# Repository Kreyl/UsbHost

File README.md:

# UsbHost
PCB with MCU &amp; CC1101, with USB connector

This project is for manupulating Ostranna devices from PC using radio
This branch is for Magic Stick project. There are two devices in system, host and wand https://github.com/Kreyl/MagicStick.
Wand sends raw data from IMU to host and host may send commands to wand.

Protocol descrideb here (in Russian) https://docs.google.com/document/d/1Enq7OxXN71MnZqI4T44DpILLiYlTNmURxSFmcvyZTgg/edit
List of commands in Russian https://docs.google.com/document/d/1xTNT9nXQbrqk0kijIyspimRIQRoJOtMbkZyYuiGS3eA/edit#heading=h.siqy2t4hsq6f
USB2Radio devices displays itself as virtual COM-port, you may user Terminal app to send commands or send commands from your code to serial port object. 

Archived branches are available here https://github.com/Kreyl/UsbHost/tags

We also have python module to work with USB2Radio  (in python folder). 

<details>
  <summary>Commands list:</summary> 

*get_port_list() function returns list of available comports as ['COM3', 'COM5', 'COM20' ...];

*get_device_port function returns first found port with Ostranna device (answer 'Ack 0' to 'Ping\r\n') as 'COM4';

*get_all_device_ports() returns list of comports with Ostranna devices connected 
                        (answer 'Ack 0' to 'Ping\r\n') as ['COM4', ...];

*open_port(port_id: str) takes comport as str parameter (open_port('COM4') and returns open port or None;

*send command(ser, command, parameters) send command with parameters to ser port, returns send status
              ("ok", "Bad data", "Unknown command" or "No device port") ;

*send query(ser, command, parameters) send query with parameters to ser port and returns answer;

*close_port(ser) gets result of open_port(port_id) as parameter and closes it .
</details>

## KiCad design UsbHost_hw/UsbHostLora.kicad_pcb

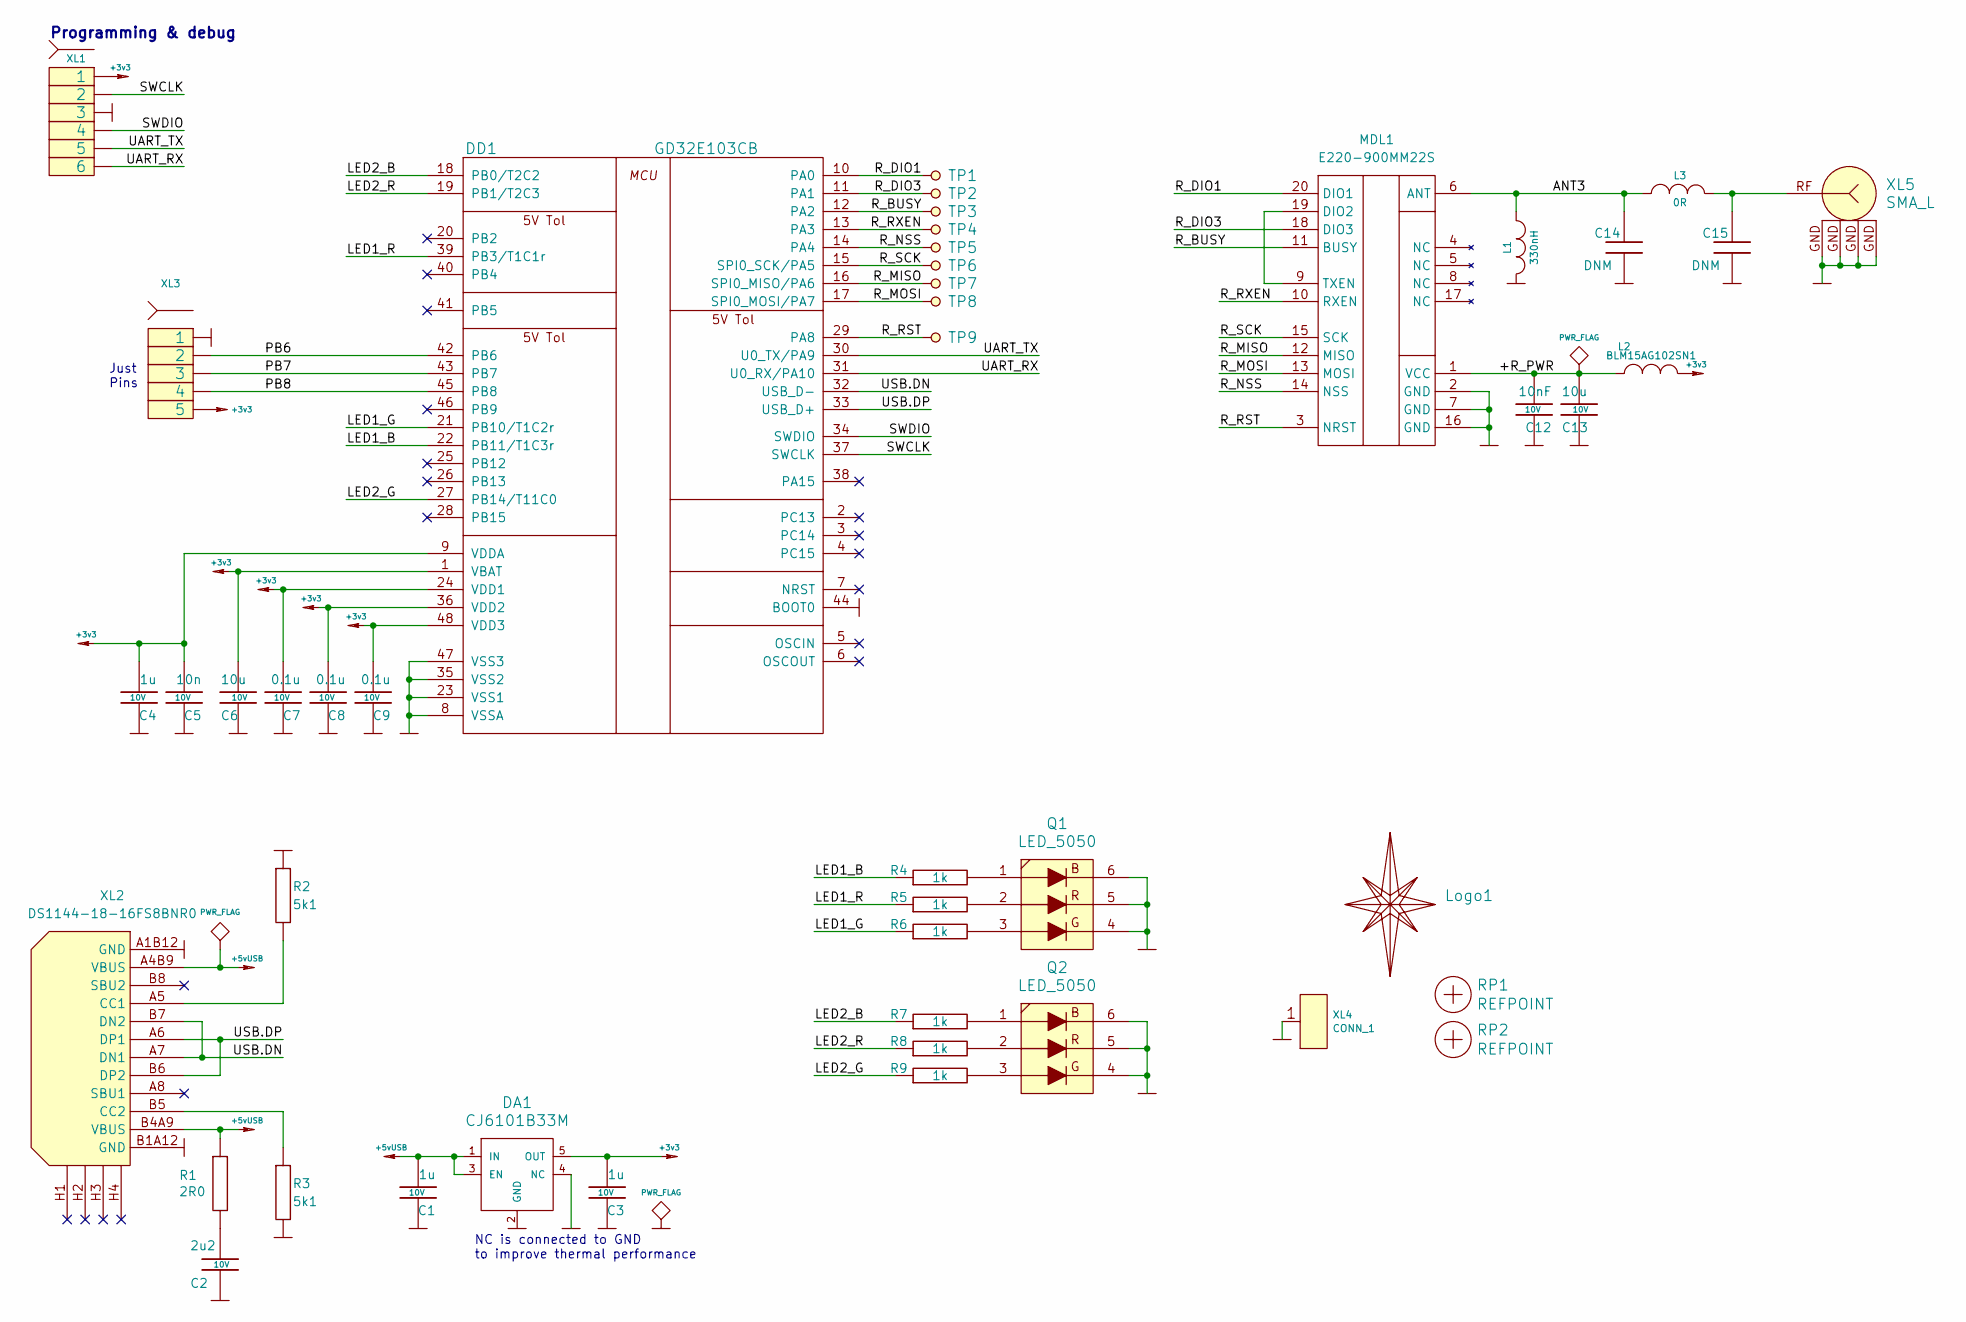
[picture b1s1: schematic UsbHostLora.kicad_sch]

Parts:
C1, C3, C4: 1u; CAP_0603_Silks; Tolerance 20%; Voltage 10V
C2: 2u2; CAP_0603_Silks; Tolerance 20%; Voltage 10V
C5: 10n; CAP_0603_Silks; Tolerance 20%; Voltage 10V
C6, C13: 10u; CAP_0603_Silks; Tolerance 20%; Voltage 10V
C7, C8, C9: 0.1u; CAP_0603_Silks; Tolerance 20%; Voltage 10V
C12: 10nF; CAP_0603_Silks; Tolerance 20%; Voltage 10V
C14, C15: DNM; CAP_0402_Silks; Tolerance 20%; Voltage 10V
DA1: CJ6101B33M; SOT23-5
DD1: GD32E103CB; LQFP48
L1: 330nH; IND_0402; Tolerance 20%
L2: BLM15AG102SN1; IND_0402; Tolerance 20%
L3: 0R; IND_0402; Tolerance 20%
Logo1: Logo; Ostranna_12d7_10d1
MDL1: E220-900MM22S
Q1, Q2: LED_5050
R1: 2R0; RES_0603_RefFab; Tolerance 1%
R2, R3: 5k1; RES_0603_RefFab; Tolerance 1%
R4, R5, R6, R7, R8, R9: 1k; RES_0603_RefFab; Tolerance 1%
RP1, RP2: REFPOINT; REF_POINT_1MM
TP1, TP2, TP3, TP4, TP5, TP6, TP7, TP8, TP9: TESTPOINT; TESTPOINT_1MM
XL1: SOCKET_6; PLS-6_LOCK
XL2: DS1144-18-16FS8BNR0; USBC_10PF-074_1
XL3: SOCKET_5; PLS-5
XL4: CONN_1; OSCIL_GND
XL5: SMA_L; SMA_R

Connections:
+3v3: C3.1, C4.1, C5.1, C6.1, C7.1, C8.1, C9.1, DA1.5 (OUT), DD1.1 (VBAT), DD1.9 (VDDA), DD1.24 (VDD1), DD1.36 (VDD2), DD1.48 (VDD3), L2.1, XL1.1, XL3.5
+5vUSB: C1.1, DA1.1 (IN), DA1.3 (EN), R1.1, XL2.A4B9 (VBUS), XL2.B4A9 (VBUS)
/+R_PWR: C12.1, C13.1, L2.2, MDL1.1 (VCC)
/ANT3: C14.1, L1.2, L3.2, MDL1.6 (ANT)
/LED1_B: DD1.22 (PB11/T1C3r), R4.1
/LED1_G: DD1.21 (PB10/T1C2r), R6.1
/LED1_R: DD1.39 (PB3/T1C1r), R5.1
/LED2_B: DD1.18 (PB0/T2C2), R7.1
/LED2_G: DD1.27 (PB14/T11C0), R9.1
/LED2_R: DD1.19 (PB1/T2C3), R8.1
/PB6: DD1.42 (PB6), XL3.2
/PB7: DD1.43 (PB7), XL3.3
/PB8: DD1.45 (PB8), XL3.4
/R_BUSY: DD1.12 (PA2), MDL1.11 (BUSY), TP3.1
/R_DIO1: DD1.10 (PA0), MDL1.20 (DIO1), TP1.1
/R_DIO3: DD1.11 (PA1), MDL1.18 (DIO3), TP2.1
/R_MISO: DD1.16 (SPI0_MISO/PA6), MDL1.12 (MISO), TP7.1
/R_MOSI: DD1.17 (SPI0_MOSI/PA7), MDL1.13 (MOSI), TP8.1
/R_NSS: DD1.14 (PA4), MDL1.14 (NSS), TP5.1
/R_RST: DD1.29 (PA8), MDL1.3 (NRST), TP9.1
/R_RXEN: DD1.13 (PA3), MDL1.10 (RXEN), TP4.1
/R_SCK: DD1.15 (SPI0_SCK/PA5), MDL1.15 (SCK), TP6.1
/SWCLK: DD1.37 (SWCLK), XL1.2
/SWDIO: DD1.34 (SWDIO), XL1.4
/UART_RX: DD1.31 (U0_RX/PA10), XL1.6
/UART_TX: DD1.30 (U0_TX/PA9), XL1.5
/USB.DN: DD1.32 (USB_D-), XL2.A7 (DN1), XL2.B7 (DN2)
/USB.DP: DD1.33 (USB_D+), XL2.A6 (DP1), XL2.B6 (DP2)
GND: C1.2, C2.2, C3.2, C4.2, C5.2, C6.2, C7.2, C8.2, C9.2, C12.2, C13.2, C14.2, C15.2, DA1.2 (GND), DA1.4 (NC), DD1.8 (VSSA), DD1.23 (VSS1), DD1.35 (VSS2), DD1.44 (BOOT0), DD1.47 (VSS3), L1.1, MDL1.2 (GND), MDL1.7 (GND), MDL1.16 (GND), Q1.4 (B), Q1.5 (G), Q1.6, Q2.4 (B), Q2.5 (G), Q2.6, R2.1, R3.2, XL1.3, XL2.A1B12 (GND), XL2.B1A12 (GND), XL3.1, XL4.1 (P1_1), XL5.GND
unnamed: C2.1, R1.2
unnamed: C15.1, L3.1, XL5.RF
unnamed: MDL1.9 (TXEN), MDL1.19 (DIO2)
unnamed: Q1.1, R4.2
unnamed: Q1.2, R5.2
unnamed: Q1.3, R6.2
unnamed: Q2.1, R7.2
unnamed: Q2.2, R8.2
unnamed: Q2.3, R9.2
unnamed: R2.2, XL2.A5 (CC1)
unnamed: R3.1, XL2.B5 (CC2)

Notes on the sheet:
Just Pins
NC is connected to GND to improve thermal performance
Programming & debug

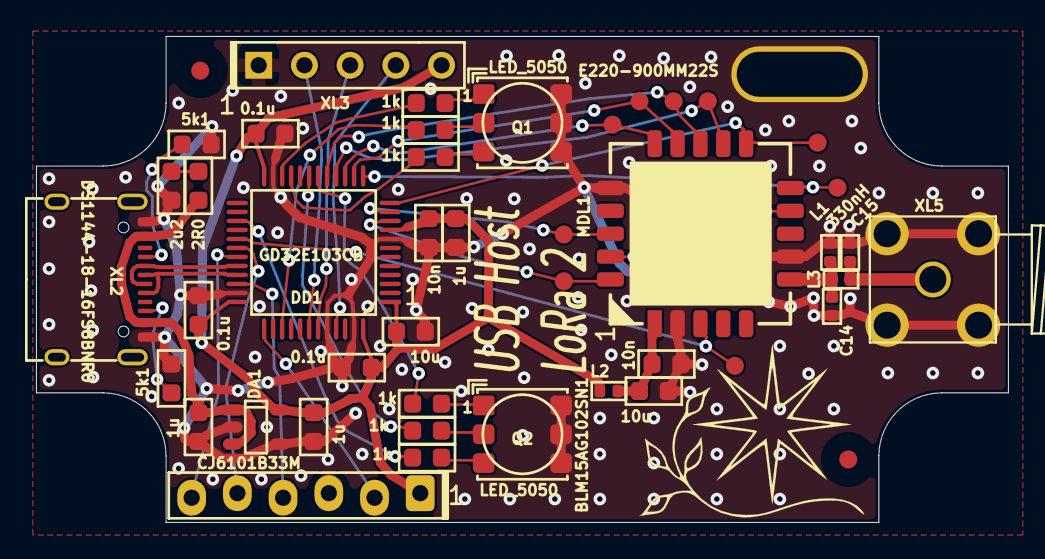
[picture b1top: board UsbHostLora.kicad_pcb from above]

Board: 2 copper layers, 54.0 x 27.0 mm, 47 parts (0 on the bottom side), 40 nets.

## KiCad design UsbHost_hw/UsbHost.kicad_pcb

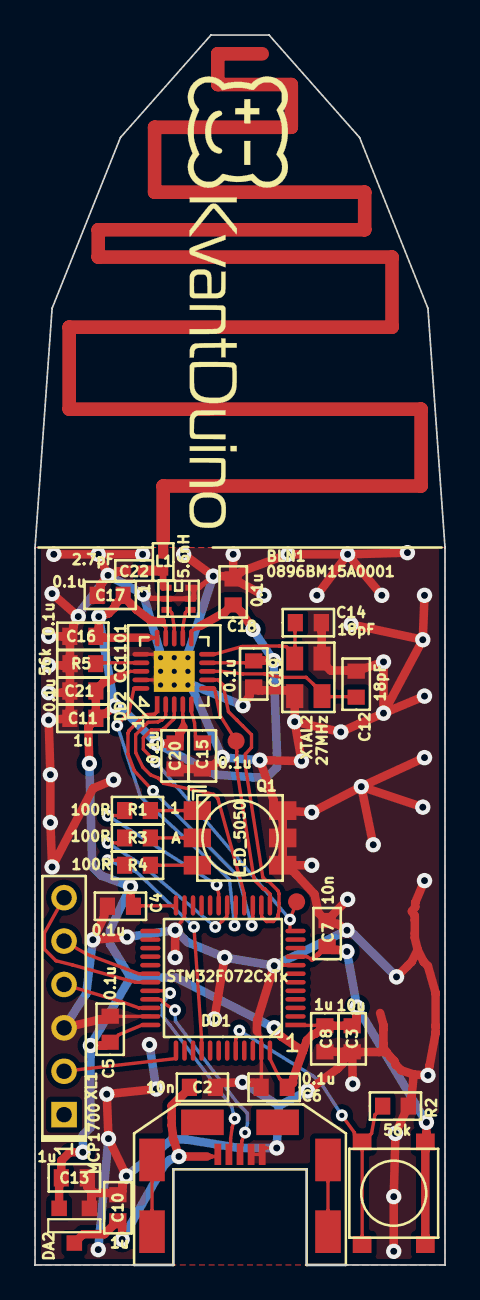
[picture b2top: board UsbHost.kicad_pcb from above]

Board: 2 copper layers, 24.0 x 72.0 mm, 40 parts (1 on the bottom side), 30 nets.

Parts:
ANT1: ANT_PCB_MONO; ANT_868_SEIDHE
BLN1: 0896BM15A0001; BALUN_JOHANSON868
C2, C7: 10n; CAP_0603
C3: 10u; CAP_0603
C4, C5, C6, C15, C16, C17, C18, C19, C20, C21: 0.1u; CAP_0603
C8, C10, C11, C13: 1u; CAP_0603
C12, C14: 18pF; CAP_0603
C22: 2.7pF; CAP_0402
DA2: MCP1700; SOT23-3
DD1: STM32F072CxTx; LQFP48
DD2: CC1101; QFN20
L1: 5.6nH; IND_0402
Logo1: Logo; KvantduinoLogoText_26d6
Logo3: Logo; MadeInRussia_22d8
Q1: LED_5050
R1, R3, R4: 100R; RES_0603
R2, R5: 56k; RES_0603
SW1: BUTTON; BTN_4x4_SMD
TP1, TP2: TESTPOINT; TESTPOINT_1MM
XL1: CONN_6; PLS-6
XL3: USB_MINI_B; USBmicro_MOLEX_WM17142
XTAL2: 27MHz; 03225C4

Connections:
+3.3V: C3.1, C4.1, C5.1, C6.1, C7.1, C8.1, C11.1, C13.1, C16.1, C17.1, C18.1, C19.1, C20.1, C21.1, DA2.2, DD1.1, DD1.9, DD1.24, DD1.36, DD1.48, DD2.4, DD2.9, DD2.11, DD2.14, DD2.15, DD2.18, SW1.2
+5V: C2.2, C10.1, DA2.3, XL3.1
/CC_CS: DD1.14, DD2.7
/CC_GDO0: DD1.13, DD2.6, TP1.1
/CC_GDO2: DD1.12, DD2.3, TP2.1
/CC_MISO: DD1.16, DD2.2
/CC_MOSI: DD1.17, DD2.20
/CC_SCK: DD1.15, DD2.1
/D+: DD1.33, XL3.3
/D-: DD1.32, XL3.2
/LED_B: DD1.40, R4.2
/LED_G: DD1.19, R1.2
/LED_R: DD1.18, R3.2
/RF1: BLN1.4, DD2.12
/RF2: BLN1.3, DD2.13
/SWCLK: DD1.37, XL1.2
/SWDIO: DD1.34, XL1.4
/UART_RX: DD1.31, XL1.6
/UART_TX: DD1.30, XL1.5
GND: BLN1.2, BLN1.5, BLN1.6, C2.1, C3.2, C4.2, C5.2, C6.2, C7.2, C8.2, C10.2, C11.2, C12.2, C13.2, C14.2, C15.2, C16.2, C17.2, C18.2, C19.2, C20.2, C21.2, C22.2, DA2.1, DD1.8, DD1.23, DD1.35, DD1.47, DD2.16, DD2.19, DD2.PAD, Q1.4, Q1.5, Q1.6, R2.2, R5.2, XL1.3, XL3.4, XL3.5, XTAL2.H
unnamed: ANT1.1, L1.1
unnamed: BLN1.1, C22.1, L1.2
unnamed: C12.1, DD2.8, XTAL2.1
unnamed: C14.1, DD2.10, XTAL2.2
unnamed: C15.1, DD2.5
unnamed: DD1.44, R2.1, SW1.1
unnamed: DD2.17, R5.1
unnamed: Q1.1, R1.1
unnamed: Q1.2, R3.1
unnamed: Q1.3, R4.1

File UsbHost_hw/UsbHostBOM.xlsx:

Reference | Value | Footprint | Quantity | SolderPointsDIP | Price | SolderPoints | Sum
BLN1 | 0896BM15A0001 | Radio:BALUN_JOHANSON868 | 1
C1 C12 C14 C9 | 18pF | Capacitors:CAP_0603 | 4
C22 | 2.7pF | Capacitors:CAP_0402 | 1
C3 | 10u | Capacitors:CAP_0603 | 1
C15 C16 C17 C18 C19 C20 C21 C4 C5 C6 | 0.1u | Capacitors:CAP_0603 | 10
C2 C7 | 10n | Capacitors:CAP_0603 | 2
C10 C11 C13 C8 | 1u | Capacitors:CAP_0603 | 4
DA1 | NCP583SQ | SOT:SC82AB | 0
DA2 | MCP1700 | SOT:SOT23-3 | 1 |  | 10 | 3
DD1 | STM32F072CxTx | LQFP_TQFP:LQFP48 | 1
DD2 | CC1101 | QFN_DFN:QFN20 | 1
L1 | 5.6nH | Inductors:IND_0402 | 1
Q1 | LED_5050 | LEDs:LED_5050 | 1 |  | 7 | 6
R1 R3 R4 | 100R | Resistors:RES_0603 | 3
R2 R5 | 56k | Resistors:RES_0603 | 2
R6 | 1k | Resistors:RES_0603 | 1 |  | 0.5 | 2
SW1 | BUTTON | BtnsSwitches:BTN_4x4_SMD | 1
XL1 | CONN_6 | Connectors:PLS-6 | 0 | 6
XL3 | USB_MINI_B | Connectors:USBmicro_MOLEX_WM17142 | 1
XTAL1 | 12MHz | Quartz:0503x4-4 | 0 |  | 15 | 4
XTAL2 | 27MHz | Quartz:03225C4 | 1

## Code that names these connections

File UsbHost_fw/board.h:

/*
 * board.h
 *
 *  Created on: 01.02.2017
 *      Author: Kreyl
 */

#ifndef BOARD_H__
#define BOARD_H__

// ==== General ====
#define BOARD_NAME          "UsbHostLora"
#define APP_NAME            "UsbHostFlasks"

// MCU type as defined in the ST header.
#define STM32F072xB     // no matter, 8 or B

// Freq of external crystal if any. Leave it here even if not used.
#define CRYSTAL_FREQ_HZ         12000000

// Ch timer
#define STM32_ST_IRQ_PRIORITY   2
#define STM32_ST_USE_TIMER      2
#define SYS_TIM_CLK             (Clk.APBFreqHz)

#define SIMPLESENSORS_ENABLED   FALSE
#define BUTTONS_ENABLED         FALSE
#define ADC_REQUIRED            FALSE
#define I2C1_ENABLED            FALSE
#define I2C_USE_SEMAPHORE       FALSE

#if 1 // ========================== GPIO =======================================
// PortMinTim_t: GPIO, Pin, Tim, TimChnl, invInverted, omPushPull, TopValue

// UART
#define UART_GPIO       GPIOA
#define UART_TX_PIN     9
#define UART_RX_PIN     10

// USB
#define USB_DM          GPIOA, 11
#define USB_DP          GPIOA, 12

// LED
#define LED_R_PIN       { GPIOC, 6, TIM3, 1, invNotInverted, omPushPull, 255 }
#define LED_G_PIN       { GPIOC, 8, TIM3, 2, invNotInverted, omPushPull, 255 }
#define LED_B_PIN       { GPIOC, 7, TIM3, 3, invNotInverted, omPushPull, 255 }

// ==== Lora ====
#define SX_SPI          SPI1
#define SX_SCK          GPIOA,  5, omPushPull, pudNone, AF0
#define SX_MISO         GPIOA,  6, omPushPull, pudNone, AF0
#define SX_MOSI         GPIOA,  7, omPushPull, pudNone, AF0
#define SX_NSS          GPIOA, 4
#define SX_NRESET       GPIOC, 3
#define SX_DIO0_GPIO    GPIOA
#define SX_DIO0_PIN     0
#define SX_DIO1_GPIO    GPIOA
#define SX_DIO1_PIN     1
#define SX_DIO2_GPIO    GPIOA
#define SX_DIO2_PIN     2
#define SX_DIO3_GPIO    GPIOA
#define SX_DIO3_PIN     3
#define SX_DIO4_GPIO    GPIOC
#define SX_DIO4_PIN     4
#define SX_DIO5_GPIO    GPIOC
#define SX_DIO5_PIN     5

#endif // GPIO

#if 1 // ========================== USB ========================================
#define USBDrv          USBD1   // USB driver to use

// CRS
#define CRS_PRESCALER   RCC_CRS_SYNC_DIV1
#define CRS_SOURCE      RCC_CRS_SYNC_SOURCE_USB
#define CRS_POLARITY    RCC_CRS_SYNC_POLARITY_RISING
#define CRS_RELOAD_VAL  ((48000000 / 1000) - 1) // Ftarget / Fsync - 1
#define CRS_ERROR_LIMIT 34
#define HSI48_CALIBRATN 32
#endif

#if 1 // =========================== DMA =======================================
#define STM32_DMA_REQUIRED  TRUE
// ==== Uart ====
#define UART_DMA_TX_MODE(Chnl) (STM32_DMA_CR_CHSEL(Chnl) | DMA_PRIORITY_LOW | STM32_DMA_CR_MSIZE_BYTE | STM32_DMA_CR_PSIZE_BYTE | STM32_DMA_CR_MINC | STM32_DMA_CR_DIR_M2P | STM32_DMA_CR_TCIE)
#define UART_DMA_RX_MODE(Chnl) (STM32_DMA_CR_CHSEL(Chnl) | DMA_PRIORITY_MEDIUM | STM32_DMA_CR_MSIZE_BYTE | STM32_DMA_CR_PSIZE_BYTE | STM32_DMA_CR_MINC | STM32_DMA_CR_DIR_P2M | STM32_DMA_CR_CIRC)
#define UART_DMA_TX     STM32_DMA_STREAM_ID(1, 2)
#define UART_DMA_RX     STM32_DMA_STREAM_ID(1, 3)
#define UART_DMA_CHNL   0   // Dummy

#endif // DMA

#if 1 // ========================== USART ======================================
#define PRINTF_FLOAT_EN FALSE
#define UART_TXBUF_SZ   2048
#define UART_RXBUF_SZ   1024
#define CMD_BUF_SZ      256

#define CMD_UART        USART1


#define CMD_UART_PARAMS \
    CMD_UART, UART_GPIO, UART_TX_PIN, UART_GPIO, UART_RX_PIN, \
    UART_DMA_TX, UART_DMA_RX, UART_DMA_TX_MODE(UART_DMA_CHNL), UART_DMA_RX_MODE(UART_DMA_CHNL), \
    uartclkHSI // independent clock

#endif

#endif //BOARD_H__

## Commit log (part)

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2016-02-08 + UsbHost hw
2016-02-08 Proceeding with USB
2016-02-08 * switch to 16.1.3 + USB works ok
2016-02-08 + Radio ok
2016-02-09 * Python's Head pkt
2016-02-29 + UsbHost2 hw
2016-03-04 + USB CDC works + CC replies, radio not tuned + LED works
2016-03-05 * Antenna matched: 2.7pF, 5.6nH, 0pF
2016-03-05 + Set Cmd parsed
2016-03-06 Cmd seems transmitted
2016-03-06 TraficLt nearing completion
2016-03-14 10pF -> 18pF
2016-03-30 + case started
2016-04-01 + TrafficLight answer analyzed + Case 3D files
2016-07-27 Single armlet RX only
2016-08-19 Two armlets
2016-08-21 + Blink on/off
2016-12-12 Something
2016-12-12 Placeholders
2016-12-12 + DevMgr
2016-12-12 + Tx seems ok
2016-12-13 Seems ok
2016-12-18 More convenient startup diag
2016-12-19 Proceeding
2016-12-23 TrafficLight release of second batch
2017-03-09 Restore
2017-03-09 Everything is broken
2017-03-09 + Usb works
2017-03-10 + General polling
2017-03-11 Replacing info in queue instead of simple put, but data stream still too large fo DataGridView
2017-03-11 Buffer for device states
2017-03-11 yet another RC
2017-03-21 Release3
2017-04-15 * Param value switched to int32
2017-04-16 + GetParam
2017-04-29 * 500kBit, FEC en
2017-05-06 * RX only
2017-09-04 + USBHost HW v3
2017-09-09 + BOM
2017-10-03 * increased stability of CRS init
2018-03-02 + BOM * Switch to newer KiCAD
2018-04-18 Compiled
2018-05-12 Switch to newer system, IRQs do not work
2018-05-12 Switch to newer system, IRQs still do not work
2018-05-12 Works
2018-05-12 + Newer libs
2018-05-12 + LED
2018-05-12 + sending to USB what received
2018-05-12 + Rx indication
2018-05-24 Tindenet works simple way
2018-12-02 + USBHost 4
2018-12-02 Fighting with trafficlight
2018-12-18 + Compiled in Atollic
2018-12-19 + UART works
2018-12-19 + Rx ok
2019-01-08 + USBHost 5
2019-01-08 + Done
2019-01-19 + Pill RW ok
2019-01-28 + i2c ctrl cmd
2019-02-06 Name change Rchnl change
2019-02-24 MagicStickDouble
2019-02-24 Done
2019-04-07 Radio transmission ok
2019-04-08 Logic 80% ready
2019-04-14 + Flash + Cmd "Queue"
2019-04-14 Listener
2019-04-29 smth
2019-04-30 Seems done
2019-05-02 + SetBtnList
2019-05-02 + Lustra control
2019-05-02 Adding Pill
2019-05-02 + Pill read and write
2019-05-07 no message
2019-05-11 python code for managing host added (description see in readme soon
2019-05-27 baudrate in python module fixed
2019-06-20 fixed python module for no comport logic
2019-06-30 * Pwr -> Dmg RC
2019-08-19 Lots of changes
2019-08-20 + Power in beacon
2019-08-22 Pkt coping switched to memcpy
2019-08-22 +rssi print
2019-08-22 * Fixing bug with unaligned memory write to uint16_t
2019-11-25 + Usb2Spi
2020-02-06 fixed comment
2020-04-15 * Buf sz increased
2020-04-15 * Switch to STM32CubeIDE * CS now at PA3 * SPI RX implemented
2020-05-13 * Switch to Chibios 19.1.3
2021-05-12 Sch in progress
2021-05-12 sch done
2021-05-13 Routing done
2021-05-13 + GERBERs
2021-05-13 Minor
2021-07-12 + Antenna tuned
2021-07-17 * Switch to CubeIDE + USB works
2021-10-18 Release
2021-10-19 Release: hogwarts flasks
2022-04-24 + retries
2022-05-03 Minor changes
2024-04-20 Switch to Eclipse + time control
2024-04-20 Switch from "hidden" to "shown" logic
2025-03-24 Switch to VSCode
